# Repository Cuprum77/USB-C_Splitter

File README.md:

# USB-C_Splitter

This project is a simple solution to the problem of working with USB-PD devices on a computer that does not have a USB-PD capable port. By splitting off the standard USB 2.0 data lines to a seperate port, with only a shared ground connection. We can experiment and develop with USB PD devices on any computer with a USB 2.0 port even if it does not support USB PD.

## How to get one
Place an order at your favorite board house using the [gerber files](production/gerber.zip) in the [production](production/) folder.
Get 3 USB-C 2.0 connectors from GCT with the model number `USB4105-GF-A-120`.
Soldering should be possible by hand, although it will require a steady hand, lots of flux and a decent soldering iron. The USB-C connectors are quite small and have a lot of pins. If you are not comfortable soldering SMD components, you can always order the board with assembly from your favorite board house.

## How to use
Simply plug in your USB-PD capable device in the "Device" port, plug a cable to your computer into the "Data" port and the remaining "Power" port is now available for you to use to power your device. All ports are USB-C 2.0 compliant and should support USB 2.0 speeds.

## License
This project is licensed under the CERN License - see the [LICENSE](LICENSE) file for details

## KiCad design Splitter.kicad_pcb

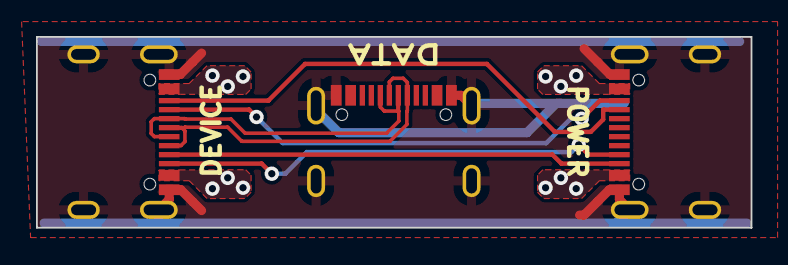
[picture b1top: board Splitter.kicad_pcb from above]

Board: 2 copper layers, 39.7 x 10.6 mm, 3 parts (0 on the bottom side), 8 nets.

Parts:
J1, J2, J4: USB4105-GF-A-120; USB_C_Receptacle_GCT_USB4105-xx-A_16P_TopMnt_Horizontal

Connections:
/CC1: J1.A5 (CC1), J2.B5 (CC2)
/CC2: J1.B5 (CC2), J2.A5 (CC1)
/D+: J1.A6 (D+), J1.B6 (D+), J4.A6 (D+), J4.B6 (D+)
/D-: J1.A7 (D-), J1.B7 (D-), J4.A7 (D-), J4.B7 (D-)
/SBU1: J1.A8 (SBU1), J2.B8 (SBU2)
/SBU2: J1.B8 (SBU2), J2.A8 (SBU1)
/VBUS: J1.A4 (VBUS), J1.A9 (VBUS), J1.B4 (VBUS), J1.B9 (VBUS), J2.A4 (VBUS), J2.A9 (VBUS), J2.B4 (VBUS), J2.B9 (VBUS)
GND: J1.A1 (GND), J1.A12 (GND), J1.B1 (GND), J1.B12 (GND), J1.S1 (SHIELD), J2.A1 (GND), J2.A12 (GND), J2.B1 (GND), J2.B12 (GND), J2.S1 (SHIELD), J4.A1 (GND), J4.A12 (GND), J4.B1 (GND), J4.B12 (GND), J4.S1 (SHIELD)

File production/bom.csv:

Designator,Footprint,Quantity,Value,LCSC Part #
"J1, J2, J4",USB_C_Receptacle_GCT_USB4105-xx-A_16P_TopMnt_Horizontal,3,"USB4105-GF-A-120
",

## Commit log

2023-05-13 fixing repo
2023-05-13 readme
2023-05-13 fixed typo
